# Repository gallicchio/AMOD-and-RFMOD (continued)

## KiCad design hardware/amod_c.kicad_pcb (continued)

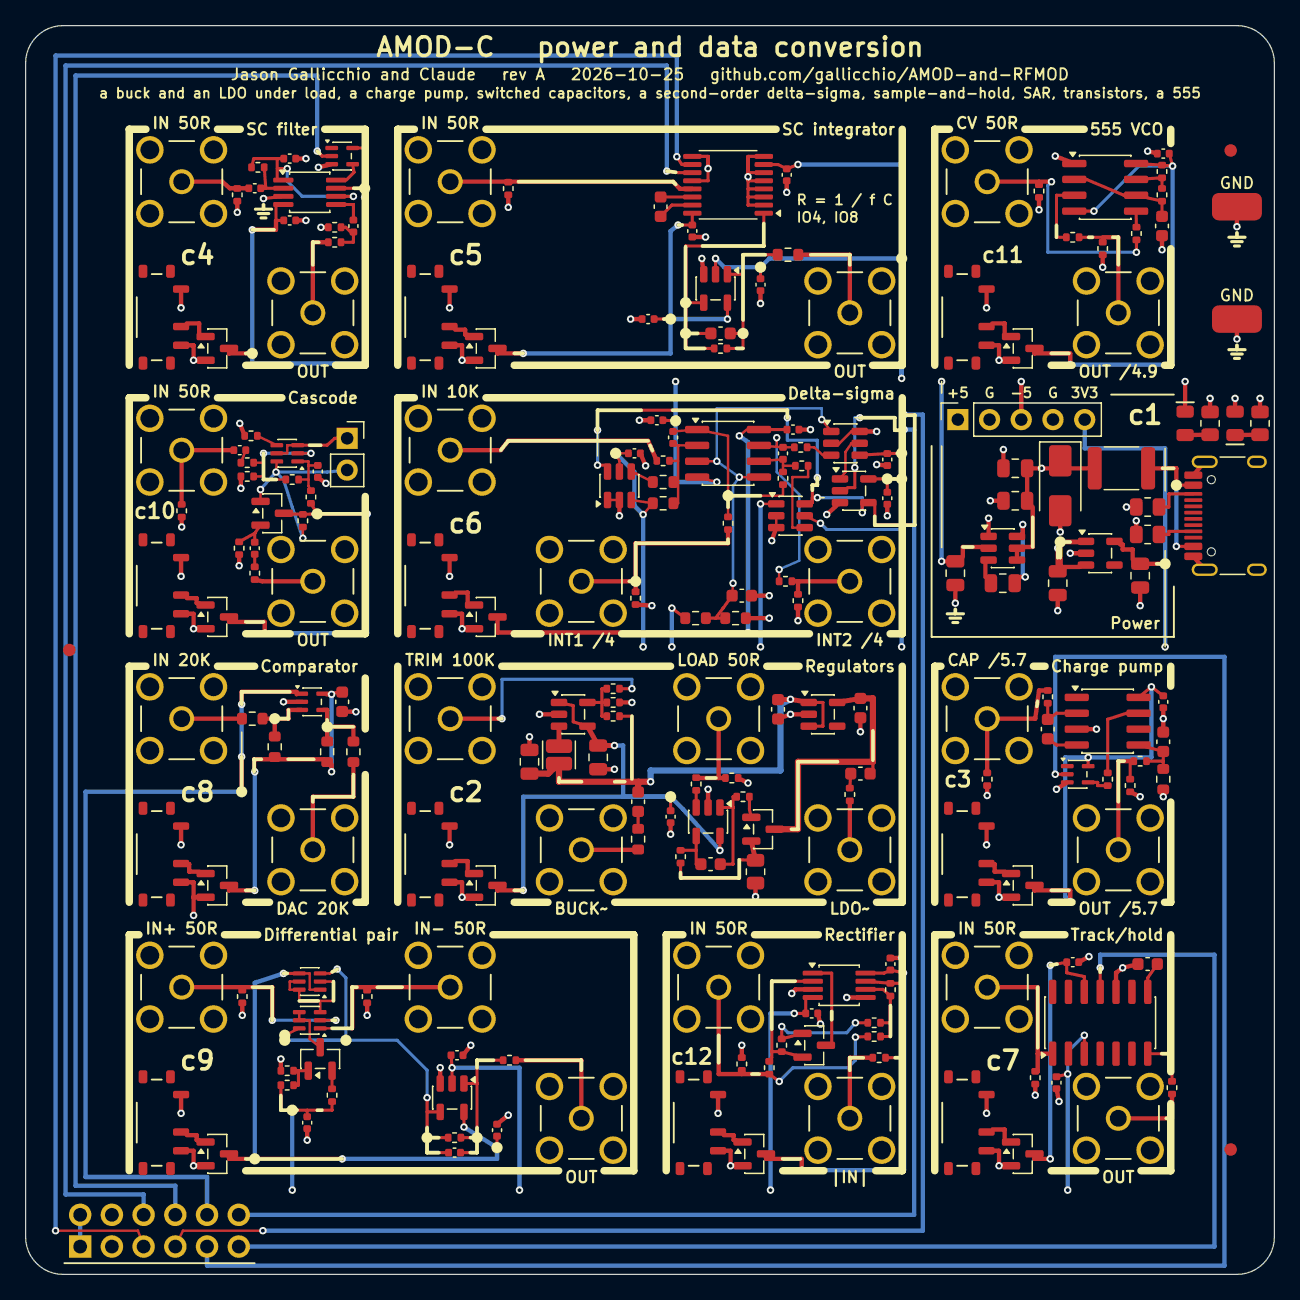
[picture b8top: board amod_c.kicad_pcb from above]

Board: 4 copper layers, 100.0 x 100.0 mm, 211 parts (0 on the bottom side), 129 nets.

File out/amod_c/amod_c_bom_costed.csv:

Comment,Designator,Footprint,LCSC Part #,MPN,Qty,Unit $,Ext $,JLC
220p,C601,C_0402_1005Metric,C39122,0402CG221J500NT,1,0.0042,0.004,extended
680p,C603,C_0402_1005Metric,C301953,0402CG681J500NT,1,0.0083,0.008,extended
100n,C801,C_0603_1608Metric,C14663,CC0603KRX7R9BB104,1,0.0084,0.008,basic
4.7p,C902,C_0402_1005Metric,C1569,0402CG4R7C500NT,1,0.0058,0.006,extended
1u,"C105,C106",C_0805_2012Metric,C28323,CL21B105KBFNNNE,2,0.0341,0.068,basic
10n,"C504,C1101",C_0603_1608Metric,C85973,GRM1885C1H103JA01D,2,0.0110,0.022,extended
1n,"C207,C501,C701",C_0603_1608Metric,C1636,0603CG102J500NT,3,0.0096,0.029,extended
1u,"C401,C404,C1001,C1003",C_0402_1005Metric,C14445,CL05A105KP5NNNC,4,0.0053,0.021,extended
10u,"C101,C102,C103,C104,C201,C202",C_0805_2012Metric,C15850,CL21A106KAYNNNE,6,0.0426,0.256,basic
1u,"C203,C204,C205,C206,C301,C303,C608",C_0603_1608Metric,C15849,CL10A105KB8NNNC,7,0.0146,0.102,basic
100n,"C208,C302,C402,C403,C502,C503,C505,C506,C602,C604,C605,C606,C607,C702,C703,C901,C903,C904,C1002,C1102,C1201,C1202",C_0402_1005Metric,C1525,CL05B104KO5NNNC,22,0.0035,0.077,basic
SMAJ5.0A,D101,D_SMA,C78401,SMAJ5.0A,1,0.0537,0.054,extended
BAT54S,D1201,SOT-23,C8592,BAT54S,1,0.0240,0.024,extended
2A,F101,Fuse_1812_4532Metric,C210837,MF-MSMF200-2,1,0.0650,0.065,extended
USB-C,J101,USB_C_Receptacle_HRO_TYPE-C-31-M-12,C165948,TYPE-C-31-M-12,1,0.1888,0.189,extended
rails,J102,PinSocket_1x05_P2.54mm_Vertical,C2894928,PZ254-1-05-Z-8.5,1,0.0588,0.059,extended
Pmod,J904,PinHeader_2x06_P2.54mm_Horizontal_PZ254R-12-12P,C492434,PZ254R-12-12P,1,0.1036,0.104,extended
CE,J1003,PinSocket_1x02_P2.54mm_Vertical,C2894925,PZ254-1-02-Z-8.5,1,0.0266,0.027,extended
SMA,"J201,J202,J203,J204,J301,J302,J401,J402,J501,J502,J601,J602,J603,J701,J702,J801,J802,J901,J902,J903,J1001,J1002,J1101,J1102,J1201,J1202",SMA_BWSMA-KE-Z001_Vertical,C496549,BWSMA-KE-Z001,26,0.4043,10.512,extended
2.2u,L201,L_Cenker_CKCS201610,C97005,WPN201610H2R2MT,1,0.0416,0.042,extended
-5V,LED101,LED_0805_2012Metric_Kbar,C84256,NCD0805R1,1,0.0135,0.013,basic
+5V,LED102,LED_0805_2012Metric_Kbar,C2297,KT-0805G,1,0.0164,0.016,basic
AO3400A,Q202,SOT-23,C20917,AO3400A,1,0.0889,0.089,basic
BCM857BS,Q902,SOT-363_SC-70-6,C105896,BCM857BS-7-F,1,0.1610,0.161,extended
DMMT3904W,"Q903,Q1002",SOT-363_SC-70-6,C155305,DMMT3904W-7-F,2,0.1594,0.319,extended
MMBT3904,"Q904,Q1003",SOT-23,C20526,MMBT3904(RANGE:100-300),2,0.0116,0.023,basic
AO3401A,"Q201,Q301,Q401,Q501,Q601,Q701,Q801,Q901,Q1001,Q1101,Q1201",SOT-23,C15127,AO3401A,11,0.0959,1.055,basic
10R,R210,R_0805_2012Metric,C17415,0805W8F100JT5E,1,0.0040,0.004,basic
1k,R303,R_0603_1608Metric,C21190,0603WAF1001T5E,1,0.0017,0.002,basic
1M,R502,R_0402_1005Metric,C26083,0402WGF1004TCE,1,0.0015,0.002,basic
33k,R1006,R_0402_1005Metric,C25779,0402WGF3302TCE,1,0.0019,0.002,basic
470R,R1008,R_0402_1005Metric,C25117,0402WGF4700TCE,1,0.0012,0.001,basic
3.9k,R1105,R_0402_1005Metric,C51721,0402WGF3901TCE,1,0.0012,0.001,extended
5.1k,"R101,R102",R_0805_2012Metric,C27834,0805W8F5101T5E,2,0.0036,0.007,basic
1k,"R103,R104",R_0805_2012Metric,C17513,0805W8F1001T5E,2,0.0035,0.007,basic
49.9,"R204,R503",R_0603_1608Metric,C6230117,SR0603FR-7T49R9L,2,0.0150,0.030,extended
47k,"R301,R305",R_0402_1005Metric,C25792,0402WGF4702TCE,2,0.0020,0.004,basic
6.8k,"R604,R903",R_0402_1005Metric,C93940,RC0402FR-076K8L,2,0.0030,0.006,extended
100R,"R209,R1004",R_0402_1005Metric,C25076,0402WGF1000TCE,2,0.0012,0.002,basic
2.2k,"R1002,R1102",R_0402_1005Metric,C25879,0402WGF2201TCE,2,0.0011,0.002,basic
3.3k,"R606,R611,R904",R_0402_1005Metric,C25890,0402WGF3301TCE,3,0.0036,0.011,basic
100k,"R201,R203,R402,R403",R_0402_1005Metric,C25741,0402WGF1003TCE,4,0.0015,0.006,basic
20k,"R202,R1005,R1204,R1206",R_0402_1005Metric,C25765,0402WGF2002TCE,4,0.0011,0.004,basic
51,"R1001,R1009,R1101,R1201",R_0402_1005Metric,C25125,0402WGF510JTCE,4,0.0012,0.005,extended
10k,"R602,R603,R609,R610,R801,R802,R803,R804",R_0603_1608Metric,C95204,RT0603BRD0710KL,8,0.0302,0.242,extended
1k,"R207,R208,R304,R607,R612,R905,R906,R1007,R1103,R1106",R_0402_1005Metric,C11702,0402WGF1001TCE,10,0.0013,0.013,basic
10k,"R302,R306,R601,R605,R608,R1003,R1104,R1202,R1203,R1205",R_0402_1005Metric,C25744,0402WGF1002TCE,10,0.0011,0.011,basic
49.9,"R205,R206,R401,R404,R501,R701,R702,R901,R902,R907,R1207",R_0402_1005Metric,C844112,CRCW040249R9FKEDHP,11,0.0318,0.350,extended
ON,"SW201,SW301,SW401,SW501,SW601,SW701,SW801,SW901,SW1001,SW1101,SW1201",SW_SPDT_Shouhan_MSK12C02,C431540,MSK12C02,11,0.0529,0.582,extended
GND,"TP9901,TP9902",TestPoint_Loop_RH-5019,C5199800,RH-5019,2,0.0966,0.193,extended
LM2664,U101,SOT-23-6,C108573,LM2664M6X/NOPB,1,0.3346,0.335,extended
3.3V,U102,SOT-23-5,C2862740,TPS7A2033PDBVR,1,0.2097,0.210,extended
TLV62568,U201,SOT-23-5,C163219,TLV62568DBVR,1,0.0750,0.075,extended
TPS7A2033,U202,SOT-23-5,C2862740,TPS7A2033PDBVR,1,0.2097,0.210,extended
ICL7660A,U302,SOIC-8_3.9x4.9mm_P1.27mm,C7881,ICL7660AIBAZA-T,1,0.9532,0.953,extended
MAX7410,U401,MSOP-8_3x3mm_P0.65mm,C17492626,MAX7410EUA+T,1,6.6211,6.621,extended
TMUX4053,U501,TSSOP-16_4.4x5mm_P0.65mm,C5377936,TMUX4053PWR,1,0.5323,0.532,extended
OPA2810,U601,SOIC-8_3.9x4.9mm_P1.27mm,C1849413,OPA2810IDR,1,2.5350,2.535,extended
TLV3501,U602,SOT-23-6,C193413,TLV3501AIDBVR,1,1.9246,1.925,extended
74LVC1G79,U603,SOT-23-5,C42878,SN74LVC1G79DBVR,1,0.1820,0.182,extended
LF398,U701,SOIC-14_3.9x8.7mm_P1.27mm,C2864267,LF398MX/NOPB,1,1.7556,1.756,extended
TLV3201,U801,SOT-353_SC-70-5,C3658542,TLV3201AQDCKRQ1,1,1.9489,1.949,extended
TLC555,U1101,SOIC-8_3.9x4.9mm_P1.27mm,C6986,TLC555CDR,1,0.2290,0.229,extended
OPA2197,U1201,MSOP-8_3x3mm_P0.65mm,C2867268,OPA2197IDGKR,1,1.8703,1.870,extended
LV1T34,"U301,U402",SOT-353_SC-70-5,C78541,SN74LV1T34DCKR,2,0.1188,0.238,extended
74LVC1G3157,"U604,U605",SOT-23-6,C10426,SN74LVC1G3157DBVR,2,0.0860,0.172,extended
OPA810,"U203,U502,U901",SOT-23-5,C2833513,OPA810IDBVR,3,3.0996,9.299,extended

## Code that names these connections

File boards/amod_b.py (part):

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    t.pwr_flags = [VMB]
    t.jack("BR", "I", "IJ", "out", "", silk="I 1V/A")
    bx = BUS_X - t.x0
    rsh = t.add("R", "R1206 0.1R", "0.1", 3.0, 3.25, 0, {"1": VM, "2": VMB}, label=None)
    t.via(VM, bx, BUS_END - t.y0)
    t.wire(VM, [(bx, BUS_END - t.y0), (rsh, "1")], width=WP)
    # VMB: a via beside the shunt, the back left to the gutter and down it to the driver
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    # slots to the left (to b7).  VDD's via is on the +3.3 V strip (the gutter between rows 1 and 2 runs under the middle)
    enc = t.add("U", "MT6701", "MT6701", cx, cy, 180, {"1": "+3V3", "3": "/ANG", "4": "GND", "6": "/ENC_DO", "7": "/PMOD4", "8": "/PMOD6"},
                hide_value=True, label=None)
    for net, pin, y in (("/ENC_DO", "6", cy - 0.635), ("/PMOD4", "7", cy + 0.635), ("/PMOD6", "8", cy + 1.905)):
        t.via(net, *ENC_VIA[net], fine=True)
        t.wire(net, [(enc, pin), ENC_VIA[net]], width=0.2)
    t.via("/ANG", *ENC_VIA["/ANG"], fine=True)
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    # the index sensor under the rim toward b9: its LED from +5 V through 180 ohm; collector and emitter on vias for b9
    a = math.radians(-60.0)
    qx, qy = cx + GIMBAL_R_INDEX * math.cos(a), cy + GIMBAL_R_INDEX * math.sin(a)
    q = t.add("U", "QRE1113GR", "QRE1113", qx, qy, 0, {"1": "QLA", "2": "GND", "3": "/IDX_C", "4": "/IDX_E"}, hide_value=True, label=None)
    rq = t.add("R", "R0805 180R", "180", qx - 0.9, qy - 4.86, 0, {"1": "+5V", "2": "QLA"}, label=None)
    t.wire("QLA", [(rq, "2"), (qx, qy - 3.6), (qx - 0.9, qy - 2.83), (q, "1")], width=W)
    t.via("+5V", qx - 3.0, qy - 4.86)
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    t.via(VMB, bx, 10.6)
    t.wire(VMB, [(drv, "8"), (23.2, Y + 0.67), (23.8, 10.27), (23.8, 10.6)], width=0.25)
    t.wire(VMB, [(23.8, 10.6), (bx, 10.6)], width=1.0)
    cvm = t.add("C", "C0402 100nF", "100n", 25.2, 12.0, 90, {"1": "GND", "2": VMB}, label=None)            # pad 2 up
    t.wire(VMB, [(cvm, "2"), (25.2, 10.9)], width=0.4)
    t.gnd_stub(cvm, "1", (26.2, 12.8), sym=(0, 0), width=W)
    cbk = t.add("C", "C0805 10uF", "10u", 28.4, 13.0, 0, {"1": "GND", "2": VMB}, label=None)
    t.wire(VMB, [(cbk, "2"), (29.35, 10.9)], width=0.6)
    t.gnd_stub(cbk, "1", (27.45, 14.4), sym=(0, 0), width=W)
    ccp = t.add("C", "C0402 100nF", "100n", 23.0, 11.9, 0, {"1": "CP", "2": VMB}, label=None)
    t.wire("CP", [(drv, "6"), (X + 0.8, 11.2), (ccp, "1")], width=F)
    t.wire(VMB, [(ccp, "2"), (23.8, 11.3), (23.8, 10.6)], width=0.25)
    # ---- EN: the three INL pins joined over the driver's top-left corner, from the comparator
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    low side only, sampled) it shows what a low-side amplifier misses."""
    t = Tile("b11", "phase current", [(3, 3)], supply="+-5 V", subtitle="INA240", sections=["Motors"])
    t.jack("BR", "IPA", "IJ", "out", "", silk="IPA 1V/A")
    rsh = t.add("R", "R1206 0.05R", "0.05", 3.6, 8.87, 0, {"1": "/PHA", "2": "/PHAM"}, label=None)
    t.wire("/PHA", [(-0.75, 8.87), (rsh, "1")], width=0.6)
    # the return to the terminal's pin 3, up and left along y 4.35
    t.wire("/PHAM", [(rsh, "2"), (5.6, 7.6), (5.6, 4.35), (-4.8, 4.35)], width=0.6)
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    t.fine = True
    F = 0.15
    imu = t.add("U", "LSM6DSO", "LSM6DSO", 10.5, 15.0, 270, {"1": "/PMOD3", "2": "GND", "3": "GND", "5": "+3V3", "6": "GND", "7": "GND", "8": "+3V3",
                                                             "12": "/PMOD8", "13": "/PMOD4", "14": "/PMOD7"}, hide_value=False, label=None)
    # SPI: the right side's three to vias staggered so the lanes on the back pass between them; MISO's from the top
    for net, pad, mid, via in (("/PMOD7", "14", [], (12.45, 14.5)), ("/PMOD8", "12", [], B6_VIA["/PMOD8"]), ("/PMOD4", "13", [], B6_VIA["/PMOD4"]),
                               ("/PMOD3", "1", [(11.25, 13.5)], (12.45, 13.5))):
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    through 49.9 ohm.  A white mark on the bell's rim gives a pulse once a turn: an index for the encoder, a tachometer."""
    t = Tile("b9", "index", [(2, 0)], supply="+-5 V", subtitle="QRE1113", sections=["Motors"])
    t.jack("BR", "IDX", "XJ", "out", "")
    ud = t.add("U", "OPA810", "OPA810", 10.6, 9.0, 0, {"1": "XO", "2": "-5V", "3": "GND", "4": "/IDX_C", "5": "+5V"}, hide_value=False, label=None)
    rf = t.add("R", "R0402 4.7k", "4.7k", 10.6, 12.0, 0, {"1": "/IDX_C", "2": "XO"}, label=None)
    cf = t.add("C", "C0402 100pF", "100p", 10.6, 13.2, 0, {"1": "/IDX_C", "2": "XO"}, label=None)
    re = t.add("R", "R0402 100R", "100", 6.0, 16.4, 0, {"1": "/IDX_E", "2": "-5V"}, label=None)
    ro = t.add("R", "R0402 49.9R", "49.9", 15.25, 10.6, 90, {"1": "XJ", "2": "XO"}, label=None)
    for (net, a, b) in (("/IDX_C", (rf, "1"), (ud, "4")), ("/IDX_C", (cf, "1"), (rf, "1")), ("XO", (rf, "2"), (ud, "1")), ("XO", (cf, "2"), (rf, "2")),
                        ("XO", (ro, "2"), (ud, "1"))):
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
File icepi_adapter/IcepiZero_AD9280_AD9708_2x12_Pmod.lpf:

# IcepiZero_AD9280_AD9708_2x12_Pmod
# HS-AD/DA V2.0 AD9280 ADC + AD9708 DAC, plus a Pmod
# GENERATED by make_boards.py from the same pin assignment as
# the PCB -- do not edit.  Rebuild with:
#     KICAD=10 ./kicad-python.sh make_boards.py

# ---- the converter module, through this adapter -------------
LOCATE COMP "ad0" SITE "R1";   # AD0, header pin 7 / GPIO4
IOBUF  PORT "ad0" IO_TYPE=LVCMOS33 PULLMODE=NONE DRIVE=4 SLEWRATE=SLOW;
LOCATE COMP "ad1" SITE "R3";   # AD1, header pin 11 / GPIO17
IOBUF  PORT "ad1" IO_TYPE=LVCMOS33 PULLMODE=NONE DRIVE=4 SLEWRATE=SLOW;
LOCATE COMP "ad2" SITE "N4";   # AD2, header pin 12 / GPIO18
IOBUF  PORT "ad2" IO_TYPE=LVCMOS33 PULLMODE=NONE DRIVE=4 SLEWRATE=SLOW;
LOCATE COMP "ad3" SITE "P3";   # AD3, header pin 13 / GPIO27
IOBUF  PORT "ad3" IO_TYPE=LVCMOS33 PULLMODE=NONE DRIVE=4 SLEWRATE=SLOW;
LOCATE COMP "ad4" SITE "P2";   # AD4, header pin 15 / GPIO22
IOBUF  PORT "ad4" IO_TYPE=LVCMOS33 PULLMODE=NONE DRIVE=4 SLEWRATE=SLOW;
LOCATE COMP "ad5" SITE "M2";   # AD5, header pin 16 / GPIO23
IOBUF  PORT "ad5" IO_TYPE=LVCMOS33 PULLMODE=NONE DRIVE=4 SLEWRATE=SLOW;
LOCATE COMP "ad6" SITE "L1";   # AD6, header pin 18 / GPIO24
IOBUF  PORT "ad6" IO_TYPE=LVCMOS33 PULLMODE=NONE DRIVE=4 SLEWRATE=SLOW;
LOCATE COMP "ad7" SITE "L2";   # AD7, header pin 19 / GPIO10
IOBUF  PORT "ad7" IO_TYPE=LVCMOS33 PULLMODE=NONE DRIVE=4 SLEWRATE=SLOW;
LOCATE COMP "aclk" SITE "J1";   # ACLK, header pin 21 / GPIO9
IOBUF  PORT "aclk" IO_TYPE=LVCMOS33 PULLMODE=NONE DRIVE=4 SLEWRATE=SLOW;
LOCATE COMP "dclk" SITE "G2";   # DCLK, header pin 23 / GPIO11
IOBUF  PORT "dclk" IO_TYPE=LVCMOS33 PULLMODE=NONE DRIVE=4 SLEWRATE=SLOW;
LOCATE COMP "da7" SITE "H2";   # DA7, header pin 24 / GPIO8
IOBUF  PORT "da7" IO_TYPE=LVCMOS33 PULLMODE=NONE DRIVE=4 SLEWRATE=SLOW;
LOCATE COMP "da6" SITE "G1";   # DA6, header pin 26 / GPIO7
IOBUF  PORT "da6" IO_TYPE=LVCMOS33 PULLMODE=NONE DRIVE=4 SLEWRATE=SLOW;
LOCATE COMP "da5" SITE "E1";   # DA5, header pin 29 / GPIO5
IOBUF  PORT "da5" IO_TYPE=LVCMOS33 PULLMODE=NONE DRIVE=4 SLEWRATE=SLOW;
LOCATE COMP "da4" SITE "F3";   # DA4, header pin 31 / GPIO6
IOBUF  PORT "da4" IO_TYPE=LVCMOS33 PULLMODE=NONE DRIVE=4 SLEWRATE=SLOW;
LOCATE COMP "da3" SITE "J3";   # DA3, header pin 32 / GPIO12
IOBUF  PORT "da3" IO_TYPE=LVCMOS33 PULLMODE=NONE DRIVE=4 SLEWRATE=SLOW;
LOCATE COMP "da2" SITE "E3";   # DA2, header pin 33 / GPIO13
IOBUF  PORT "da2" IO_TYPE=LVCMOS33 PULLMODE=NONE DRIVE=4 SLEWRATE=SLOW;
LOCATE COMP "da1" SITE "E4";   # DA1, header pin 35 / GPIO19
IOBUF  PORT "da1" IO_TYPE=LVCMOS33 PULLMODE=NONE DRIVE=4 SLEWRATE=SLOW;
LOCATE COMP "da0" SITE "D4";   # DA0, header pin 37 / GPIO26
IOBUF  PORT "da0" IO_TYPE=LVCMOS33 PULLMODE=NONE DRIVE=4 SLEWRATE=SLOW;

# ---- the Pmod socket J3: pmod[n-1] is the Pmod standard's IOn (pins 1-4, 7-10) -----
LOCATE COMP "pmod[0]" SITE "N1";   # PMOD1, socket pad 1, header pin 10 / GPIO15
IOBUF  PORT "pmod[0]" IO_TYPE=LVCMOS33 PULLMODE=NONE DRIVE=4 SLEWRATE=SLOW;
LOCATE COMP "pmod[1]" SITE "G3";   # PMOD2, socket pad 3, header pin 27 / GPIO0
IOBUF  PORT "pmod[1]" IO_TYPE=LVCMOS33 PULLMODE=NONE DRIVE=4 SLEWRATE=SLOW;
LOCATE COMP "pmod[2]" SITE "H3";   # PMOD3, socket pad 5, header pin 36 / GPIO16
IOBUF  PORT "pmod[2]" IO_TYPE=LVCMOS33 PULLMODE=NONE DRIVE=4 SLEWRATE=SLOW;
LOCATE COMP "pmod[3]" SITE "F2";   # PMOD4, socket pad 7, header pin 40 / GPIO21
IOBUF  PORT "pmod[3]" IO_TYPE=LVCMOS33 PULLMODE=NONE DRIVE=4 SLEWRATE=SLOW;
LOCATE COMP "pmod[4]" SITE "P1";   # PMOD5, socket pad 2, header pin 8 / GPIO14
IOBUF  PORT "pmod[4]" IO_TYPE=LVCMOS33 PULLMODE=NONE DRIVE=4 SLEWRATE=SLOW;
LOCATE COMP "pmod[5]" SITE "J2";   # PMOD6, socket pad 4, header pin 22 / GPIO25
IOBUF  PORT "pmod[5]" IO_TYPE=LVCMOS33 PULLMODE=NONE DRIVE=4 SLEWRATE=SLOW;
LOCATE COMP "pmod[6]" SITE "K3";   # PMOD7, socket pad 6, header pin 28 / GPIO1
IOBUF  PORT "pmod[6]" IO_TYPE=LVCMOS33 PULLMODE=NONE DRIVE=4 SLEWRATE=SLOW;
LOCATE COMP "pmod[7]" SITE "F1";   # PMOD8, socket pad 8, header pin 38 / GPIO20
IOBUF  PORT "pmod[7]" IO_TYPE=LVCMOS33 PULLMODE=NONE DRIVE=4 SLEWRATE=SLOW;

# ---- the Icepi Zero itself ----------------------------
LOCATE COMP "clk50" SITE "M1";   # 50 MHz oscillator -- the only clock on the board
IOBUF  PORT "clk50" IO_TYPE=LVCMOS33 PULLMODE=NONE;
LOCATE COMP "uart_tx" SITE "K15";   # to U9 (FT231X) RXD -> /dev/ttyUSB* on the host
IOBUF  PORT "uart_tx" IO_TYPE=LVCMOS33 PULLMODE=NONE;
LOCATE COMP "uart_rx" SITE "K16";   # from U9 (FT231X) TXD
IOBUF  PORT "uart_rx" IO_TYPE=LVCMOS33 PULLMODE=NONE;
LOCATE COMP "led0" SITE "E13";
IOBUF  PORT "led0" IO_TYPE=LVCMOS33 PULLMODE=NONE;
LOCATE COMP "led1" SITE "D14";
IOBUF  PORT "led1" IO_TYPE=LVCMOS33 PULLMODE=NONE;
LOCATE COMP "led2" SITE "E12";
IOBUF  PORT "led2" IO_TYPE=LVCMOS33 PULLMODE=NONE;
LOCATE COMP "led3" SITE "C13";
IOBUF  PORT "led3" IO_TYPE=LVCMOS33 PULLMODE=NONE;
LOCATE COMP "led4" SITE "D13";
IOBUF  PORT "led4" IO_TYPE=LVCMOS33 PULLMODE=NONE;
LOCATE COMP "btn0" SITE "C4";   # also the LiteX reset button
IOBUF  PORT "btn0" IO_TYPE=LVCMOS33 PULLMODE=UP;
LOCATE COMP "btn1" SITE "C5";
IOBUF  PORT "btn1" IO_TYPE=LVCMOS33 PULLMODE=UP;

# The oscillator, so nextpnr reports the real timing margin
# instead of guessing.
FREQUENCY PORT "clk50" 50 MHZ;

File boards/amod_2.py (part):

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    t.wire("-15V", [(cn2, "2"), (9.55, 13.75)], width=0.4)
    # PD: 4.7 k from Pmod IO1 (along the top from the gutter on the left), 10 k to ground
    rpd = t.add("R", "R0402 10k", "10k", 9.7, 5.6, 0, {"1": "GND", "2": "PD"}, label=None)
    rs = t.add("R", "R0402 4.7k", "4.7k", 11.25, 4.3, 90, {"1": "PD", "2": "/PMOD1"}, label=None)              # pad 1 down
    t.wire("PD", [(u, "16"), (11.25, 5.6), (rpd, "2")], width=F)
    t.wire("PD", [(11.25, 5.6), (rs, "1")], width=F)
    gnd(t, rpd, "1", (8.3, 5.6), w=0.2)
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    used = PMOD_USED                                       # the lines some tile uses; the others stay open on the plug
    pads = {"12": "/PMOD1", "10": "/PMOD2", "8": "/PMOD3", "6": "/PMOD4", "11": "/PMOD5", "9": "/PMOD6", "7": "/PMOD7", "5": "/PMOD8"}
    pins = {k: v for k, v in pads.items() if v in used}
    pins.update({"3": "GND", "4": "GND", "1": "/PMOD_VCC", "2": "/PMOD_VCC"})
    pm = t.add("J", "PMOD", "Pmod", 2.97, 24.25, 0, pins, hide_value=True)
    t.wire("/PMOD_VCC", [(pm, "1"), (pm, "2")], silk=False)
    t.text(1.2, 9.4, "Y5", 1.2, 0.2, "left")
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    power_header(t, rail="+5V")
    t.wire("VS", [HDR_VS, (10.2, 18.1)], width=0.35)
    # the switch: TPS22917 (rot 0: VIN 1, GND 2, ON 3 down the left; VOUT 6 top-right; CT and QOD open); ON is Pmod IO8
    sw = t.add("U", "TPS22917", "TPS22917", 3.2, 3.0, 0, {"1": "VS", "2": "GND", "3": "/PMOD8", "6": "VN"}, hide_value=False, label=None)
    t.gnd_stub(sw, "2", (3.2, 3.0), sym=(0, 0), width=0.25, fine=True)
    cvs = t.add("C", "C0402 1uF", "1u", 3.2, 0.6, 180, {"1": "VS", "2": "GND"}, label=None)                  # rot 180: VS pad right
    gnd(t, cvs, "2", (1.6, 0.6), w=0.25)
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    # U1: INC = 2 B.  rot 270: +IN (13.65, 7.26), V- (14.6, 7.26), OUT (15.55, 7.26); -IN (13.65, 9.54), V+ (15.55, 9.54)
    u1 = t.add("U", "OPA810", "OPA810", 14.6, 8.4, 270, {"1": "O1", "2": "-5V", "3": "B", "4": "N1", "5": "VS"}, hide_value=False, label=None)
    t.wire("B", [(12.1, 7.25), (u1, "3")], width=0.2)
    rf1 = t.add("R", "R0402 499R", "499", 14.8, 11.1, 0, {"1": "N1", "2": "O1"}, label=None)
    rg1 = t.add("R", "R0402 499R", "499", 12.9, 11.1, 0, {"1": "GND", "2": "N1"}, label=None)
    t.wire("N1", [(u1, "4"), (13.65, 11.1)], width=0.2)
    t.wire("N1", [(rg1, "2"), (rf1, "1")], width=0.2)
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    rg2 = t.add("R", "R0402 499R", "499", 17.5, 8.4, 270, {"1": "O1", "2": "N2"}, label=None)                  # pad 1 up
    t.wire("O1", [(16.2, 7.92), (rg2, "1")], width=0.2)
    t.wire("N2", [(rg2, "2"), (17.5, 9.54), (u2, "4")], width=0.2)
    rf2 = t.add("R", "R0402 499R", "499", 19.8, 11.1, 0, {"1": "N2", "2": "O2"}, label=None)
    t.wire("N2", [(u2, "4"), (18.85, 11.1), (rf2, "1")], width=0.2)
    ro2 = t.add("R", "R0402 49.9R", "49.9", 23.5, 10.0, 0, {"1": "O2", "2": "REFL"}, label=None)
    t.wire("O2", [(u2, "1"), (21.8, 7.26), (21.8, 10.0), (ro2, "1")], width=0.2)
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    cbulk = t.add("C", "C0805 10uF", "10u", 34.6, 9.0, 90, {"1": "GND", "2": "VS"}, label=None)                 # rot 90: pad 2 up
    t.wire("VS", [(32.3, 7.9), (34.6, 8.0875)], width=0.4)
    gnd(t, cbulk, "1", (34.6, 11.0), w=0.4)
    q3 = t.add("Q", "NFET", "AO3400A", 35.9, 2.0, 0, {"1": "/PMOD5", "2": "GND", "3": "ID"}, hide_value=False, label=None)
    gnd(t, q3, "2", (34.9625, 3.85), w=0.3)
    t.wire("ID", [(q2, "3"), (33.5, 4.6), (36.75, 4.6), (36.75, 2.0), (q3, "3")], width=0.4)
    la = t.add("L", "L0805 330nH", "330n", 36.75, 8.0, 270, {"1": "ID", "2": "LM"}, label=None)                 # pad 1 up
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    t.wire("MON", [(rmon, "1"), (30.2, 12.8), (30.2, 19.6), (19.4, 19.6), (19.4, 15.25), (jmon, "1")], width=0.25)
    # ---- IO5 along the top to the shunt's gate, 100 k holding it low
    t.wire("/PMOD5", [(-0.35, 0.25), (34.4, 0.25), (q3, "1")], width=F, silk=False)
    rsd = t.add("R", "R0402 100k", "100k", 22.0, 1.2, 270, {"1": "/PMOD5", "2": "GND"}, label=None)
    t.wire("/PMOD5", [(22.0, 0.25), (rsd, "1")], width=F)
    gnd(t, rsd, "2", (22.0, 2.7), w=0.2)
    # ---- VS on the back: the switch's drain up x 10.2 to U1; on to REF's 1 k, U2 and a 100 nF; along the gutter to the 10 ohm
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    t.wire("/PMOD6", [(9.55, 9.5), (u, "1")], width=F)
    t.via("/PMOD7", 8.95, 10.875, fine=True)
    t.wire("/PMOD7", [(8.95, 10.875), (u, "2")], width=F)
    rpd6 = t.add("R", "R0402 100k", "100k", 7.4, 9.7, 0, {"1": "GND", "2": "/PMOD6"}, label=None)
    t.wire("/PMOD6", [(rpd6, "2"), (9.55, 9.5)], width=F)
    rpd7 = t.add("R", "R0402 100k", "100k", 7.7, 10.9, 0, {"1": "GND", "2": "/PMOD7"}, label=None)
    t.wire("/PMOD7", [(rpd7, "2"), (8.95, 10.875)], width=F)
    gnd(t, rpd6, "1", (6.0, 9.7), w=0.2)
    t.wire("GND", [(rpd7, "1"), (6.4, 10.3), (6.0, 9.7)], width=0.2, silk=False)
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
